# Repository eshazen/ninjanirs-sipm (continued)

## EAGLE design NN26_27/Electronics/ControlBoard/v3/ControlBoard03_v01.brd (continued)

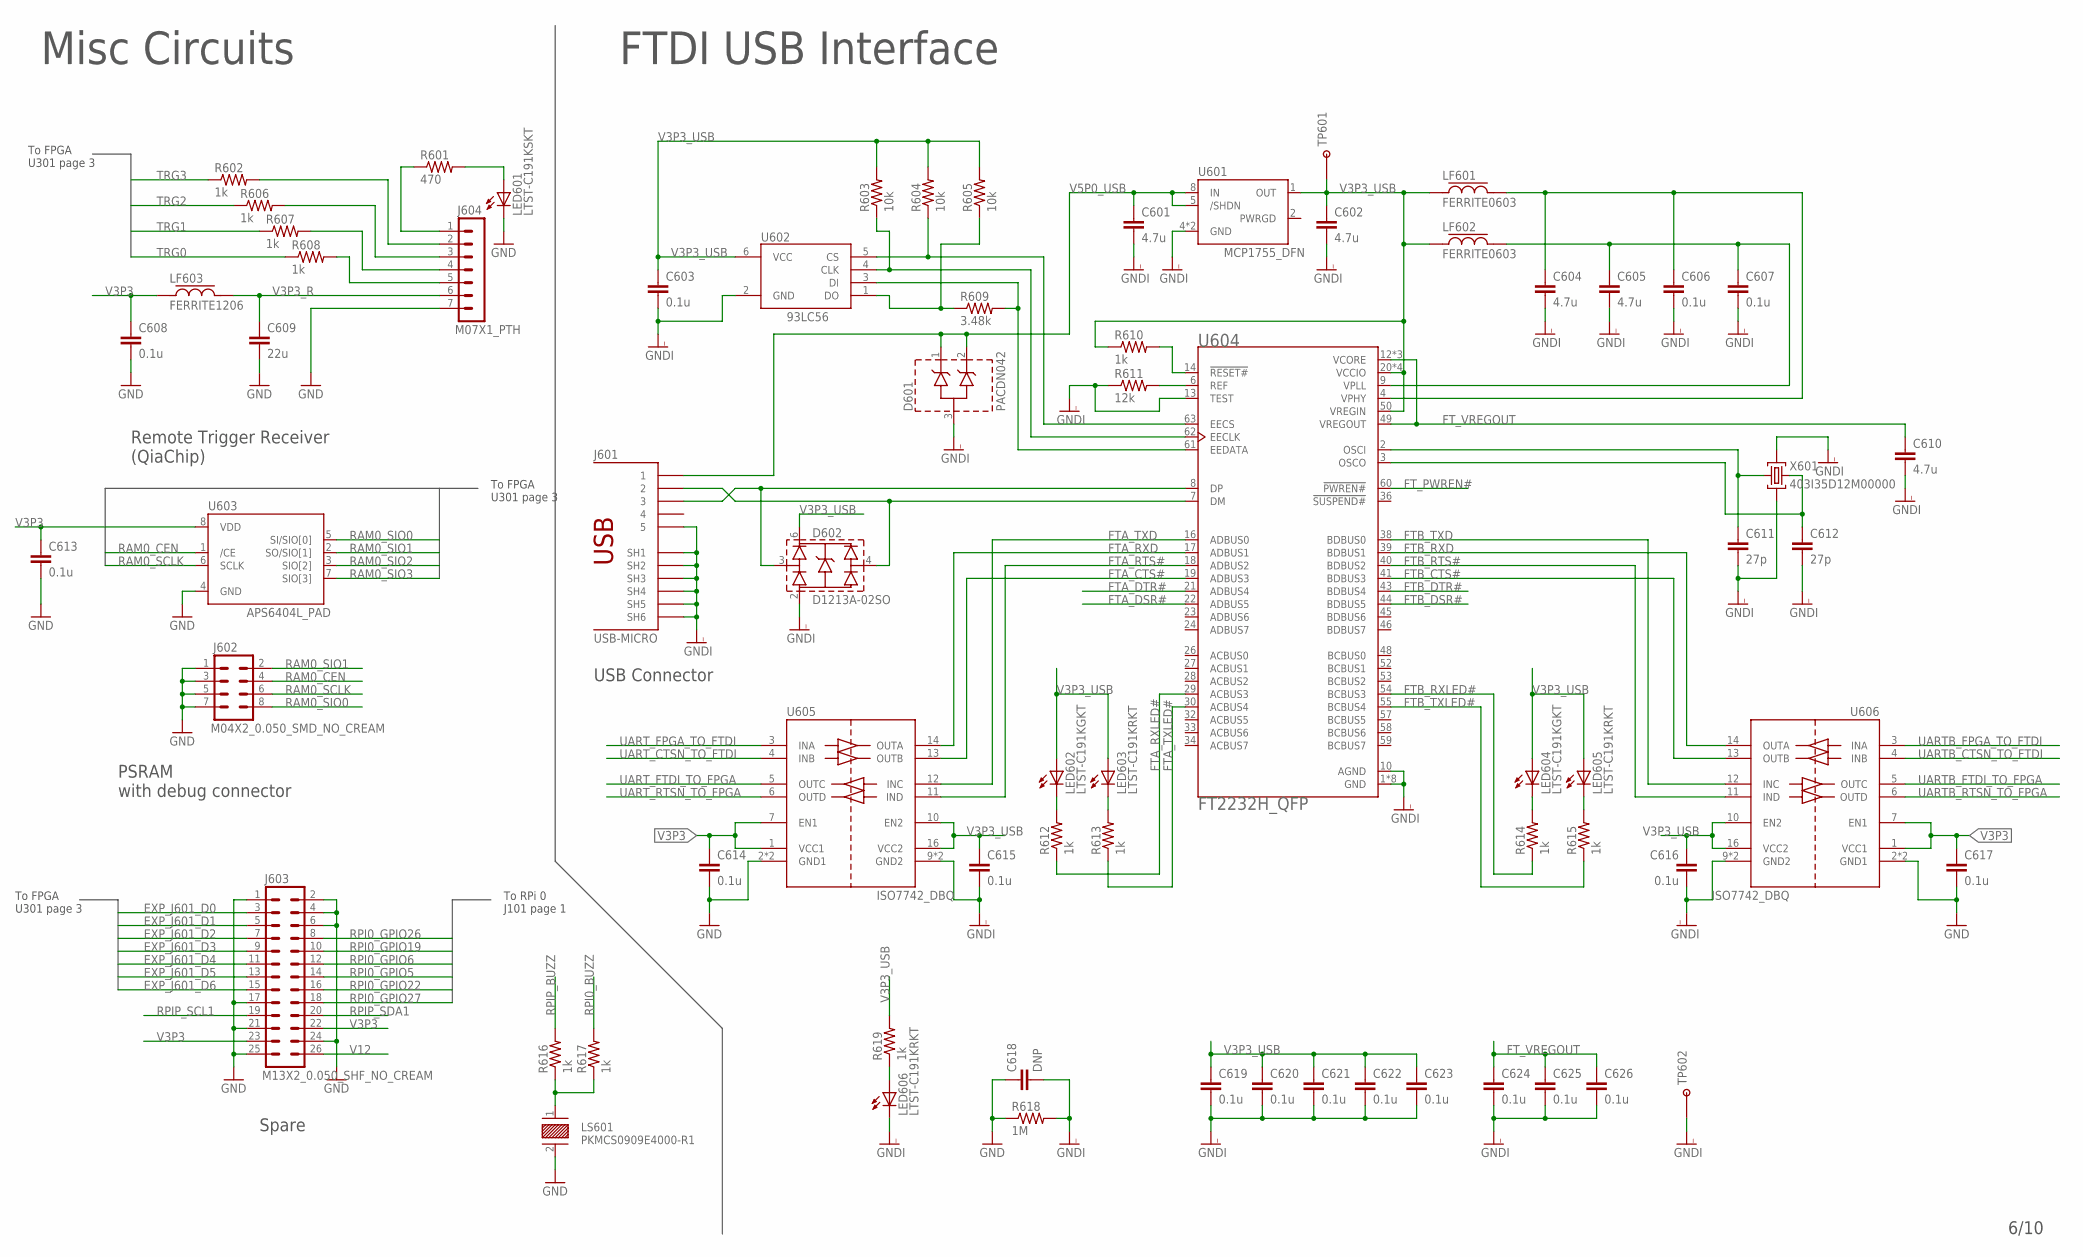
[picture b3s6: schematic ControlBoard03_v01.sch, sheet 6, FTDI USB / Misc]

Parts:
C601, C602, C604, C605, C610: 4.7u; 0402-CAP
C603, C606, C607, C608, C613, C614, C615, C616, C617, C619, C620, C621, C622, C623, C624, C625, C626: 0.1u; 0402-CAP
C609: 22u; 0805-CAP
C611, C612: 27p; 0402-CAP
C618: DNP; 1210
D601: PACDN042; SOT23-3
D602: D1213A-02SO; SOT23-6
J601: USB-MICRO
J602: M04X2_0.050_SMD_NO_CREAM
J603: M13X2_0.050_SHF_NO_CREAM
J604: M07X1_PTH
LED601: LTST-C191KSKT; LED-0603
LED602, LED604: LTST-C191KGKT; LED-0603
LED603, LED605, LED606: LTST-C191KRKT; LED-0603
LF601, LF602: FERRITE0603; 0603-FER
LF603: FERRITE1206; 1206
LS601: PKMCS0909E4000-R1; XDCR_PKMCS0909E4000-R1
R601: 470; 0402-RES
R602, R606, R607, R608, R610, R612, R613, R614, R615, R616, R617, R619: 1k; 0402-RES
R603, R604, R605: 10k; 0402-RES
R609: 3.48k; 0402-RES
R611: 12k; 0402-RES
R618: 1M; R2010
TP601: TESTPOINT_ROUND; TESTPAD_ROUND
TP602: TESTPOINT1X01; 1X01
U601: MCP1755_DFN; DFN8_2X3MM
U602: 93LC56; SOT23-6
U603: APS6404L_PAD; USON8L-2X3MM_APM
U604: FT2232H_QFP; QFP50P1200X1200X160-64N
U605, U606: ISO7742_DBQ; SSOP16
X601: 403I35D12M00000; CRYSTAL-3.2-2.5

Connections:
EXP_J601_D0: J603.3; also elsewhere on the board
EXP_J601_D1: J603.5; also elsewhere on the board
EXP_J601_D2: J603.7; also elsewhere on the board
EXP_J601_D3: J603.9; also elsewhere on the board
EXP_J601_D4: J603.11; also elsewhere on the board
EXP_J601_D5: J603.13; also elsewhere on the board
EXP_J601_D6: J603.15; also elsewhere on the board
FTA_CTS#: U604.19 (ADBUS3), U605.13 (OUTB)
FTA_DSR#: U604.22 (ADBUS5)
FTA_DTR#: U604.21 (ADBUS4)
FTA_RTS#: U604.18 (ADBUS2), U605.11 (IND)
FTA_RXD: U604.17 (ADBUS1), U605.14 (OUTA)
FTA_RXLED#: R612.1, U604.29 (ACBUS3)
FTA_TXD: U604.16 (ADBUS0), U605.12 (INC)
FTA_TXLED#: R613.1, U604.30 (ACBUS4)
FTB_CTS#: U604.41 (BDBUS3), U606.13 (OUTB)
FTB_DSR#: U604.44 (BDBUS5)
FTB_DTR#: U604.43 (BDBUS4)
FTB_RTS#: U604.40 (BDBUS2), U606.11 (IND)
FTB_RXD: U604.39 (BDBUS1), U606.14 (OUTA)
FTB_RXLED#: R614.1, U604.54 (BCBUS3)
FTB_TXD: U604.38 (BDBUS0), U606.12 (INC)
FTB_TXLED#: R615.1, U604.55 (BCBUS4)
FT_PWREN#: U604.60 (!PWREN#)
FT_VREGOUT: C610.1, C624.1, C625.1, C626.1, U604.12 (VCORE), U604.37 (VCORE), U604.49 (VREGOUT), U604.64 (VCORE)
GND: C608.2, C609.2, C613.2, C614.2, C617.2, C618.1, J602.1, J602.3, J602.5, J602.7, J603.1, J603.2, J603.4, J603.6, J603.17, J603.21, J603.24, J603.25, J604.7, LED601.C, LS601.2, R618.1, U603.4 (GND), U605.2 (GND1), U605.8 (GND1), U606.2 (GND1), U606.8 (GND1); also elsewhere on the board
GNDI: C601.2, C602.2, C603.2, C604.2, C605.2, C606.2, C607.2, C610.2, C611.2, C612.2, C615.2, C616.2, C618.2, C619.2, C620.2, C621.2, C622.2, C623.2, C624.2, C625.2, C626.2, D601.3 (A), D602.2 (VN), J601.5, J601.SH1, J601.SH2, J601.SH3, J601.SH4, J601.SH5, J601.SH6, LED606.C, R611.1, R618.2, TP602.1, U601.4 (GND), U601.P (GND), U602.2 (GND), U604.1 (GND), U604.5 (GND), U604.10 (AGND), U604.11 (GND), U604.13 (TEST), U604.15 (GND), U604.25 (GND), U604.35 (GND), U604.47 (GND), U604.51 (GND), U605.9 (GND2), U605.15 (GND2), U606.9 (GND2), U606.15 (GND2), X601.2 (GND), X601.4 (GND)
LED: J604.1, R601.1
unnamed: LED606.A, R619.1
unnamed: R604.1, U602.5 (CS), U604.63 (EECS)
unnamed: R603.1, U602.4 (CLK), U604.62 (EECLK)
unnamed: R605.1, R609.1, U602.1 (DO)
unnamed: LS601.1, R616.1, R617.1
unnamed: R609.2, U602.3 (DI), U604.61 (EEDATA)
unnamed: C605.1, C607.1, LF602.2, U604.9 (VPLL)
unnamed: C604.1, C606.1, LF601.2, U604.4 (VPHY)
unnamed: R610.2, U604.14 (!RESET#)
unnamed: R611.2, U604.6 (REF)
unnamed: C611.1, U604.2 (OSCI), X601.1 (C1)
unnamed: C612.1, U604.3 (OSCO), X601.3 (C2)
unnamed: LED604.C, R614.2
unnamed: LED605.C, R615.2
unnamed: LED602.C, R612.2
unnamed: LED603.C, R613.2
unnamed: D602.3 (CH1), J601.3, U604.8 (DP)
unnamed: D602.4 (CH2), J601.2, U604.7 (DM)
unnamed: J604.5, R608.2
unnamed: J604.4, R607.2
unnamed: J604.3, R606.2
unnamed: J604.2, R602.2
unnamed: LED601.A, R601.2
RAM0_CEN: J602.4, U603.1 (/CE); also elsewhere on the board
RAM0_SCLK: J602.6, U603.6 (SCLK); also elsewhere on the board
RAM0_SIO0: J602.8, U603.5 (SI/SIO[0]); also elsewhere on the board
RAM0_SIO1: J602.2, U603.2 (SO/SIO[1]); also elsewhere on the board
RAM0_SIO2: U603.3 (SIO[2]); also elsewhere on the board
RAM0_SIO3: U603.7 (SIO[3]); also elsewhere on the board
RPI0_BUZZ: R617.2; also elsewhere on the board
RPI0_GPIO5: J603.14; also elsewhere on the board
RPI0_GPIO6: J603.12; also elsewhere on the board
RPI0_GPIO19: J603.10; also elsewhere on the board
RPI0_GPIO22: J603.16; also elsewhere on the board
RPI0_GPIO26: J603.8; also elsewhere on the board
RPI0_GPIO27: J603.18; also elsewhere on the board
RPIP_BUZZ: R616.2; also elsewhere on the board
RPIP_SCL1: J603.19; also elsewhere on the board
RPIP_SDA1: J603.20; also elsewhere on the board
TRG0: R608.1; also elsewhere on the board
TRG1: R607.1; also elsewhere on the board
TRG2: R606.1; also elsewhere on the board
TRG3: R602.1; also elsewhere on the board
UARTB_CTSN_TO_FTDI: U606.4 (INB); also elsewhere on the board
UARTB_FPGA_TO_FTDI: U606.3 (INA); also elsewhere on the board
UARTB_FTDI_TO_FPGA: U606.5 (OUTC); also elsewhere on the board
UARTB_RTSN_TO_FPGA: U606.6 (OUTD); also elsewhere on the board
UART_CTSN_TO_FTDI: U605.4 (INB); also elsewhere on the board
UART_FPGA_TO_FTDI: U605.3 (INA); also elsewhere on the board
UART_FTDI_TO_FPGA: U605.5 (OUTC); also elsewhere on the board
UART_RTSN_TO_FPGA: U605.6 (OUTD); also elsewhere on the board
V3P3: C608.1, C613.1, C614.1, C617.1, J603.22, J603.23, LF603.1, U603.8 (VDD), U605.1 (VCC1), U605.7 (EN1), U606.1 (VCC1), U606.7 (EN1); also elsewhere on the board
V3P3_R: C609.1, J604.6, LF603.2
V3P3_USB: C602.1, C603.1, C615.1, C616.1, C619.1, C620.1, C621.1, C622.1, C623.1, D602.6 (VP), LED602.A, LED603.A, LED604.A, LED605.A, LF601.1, LF602.1, R603.2, R604.2, R605.2, R610.1, R619.2, TP601.P$1, U601.1 (OUT), U602.6 (VCC), U604.20 (VCCIO), U604.31 (VCCIO), U604.42 (VCCIO), U604.50 (VREGIN), U604.56 (VCCIO), U605.10 (EN2), U605.16 (VCC2), U606.10 (EN2), U606.16 (VCC2)
V5P0_USB: C601.1, D601.1 (C), D601.2 (C), J601.1, U601.5 (/SHDN), U601.8 (IN)
V12: J603.26; also elsewhere on the board

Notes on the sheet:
Misc Circuits
Remote Trigger Receiver (QiaChip)
PSRAM with debug connector
Spare
To FPGA U301 page 3
To RPi 0 J101 page 1
FTDI USB Interface
USB Connector

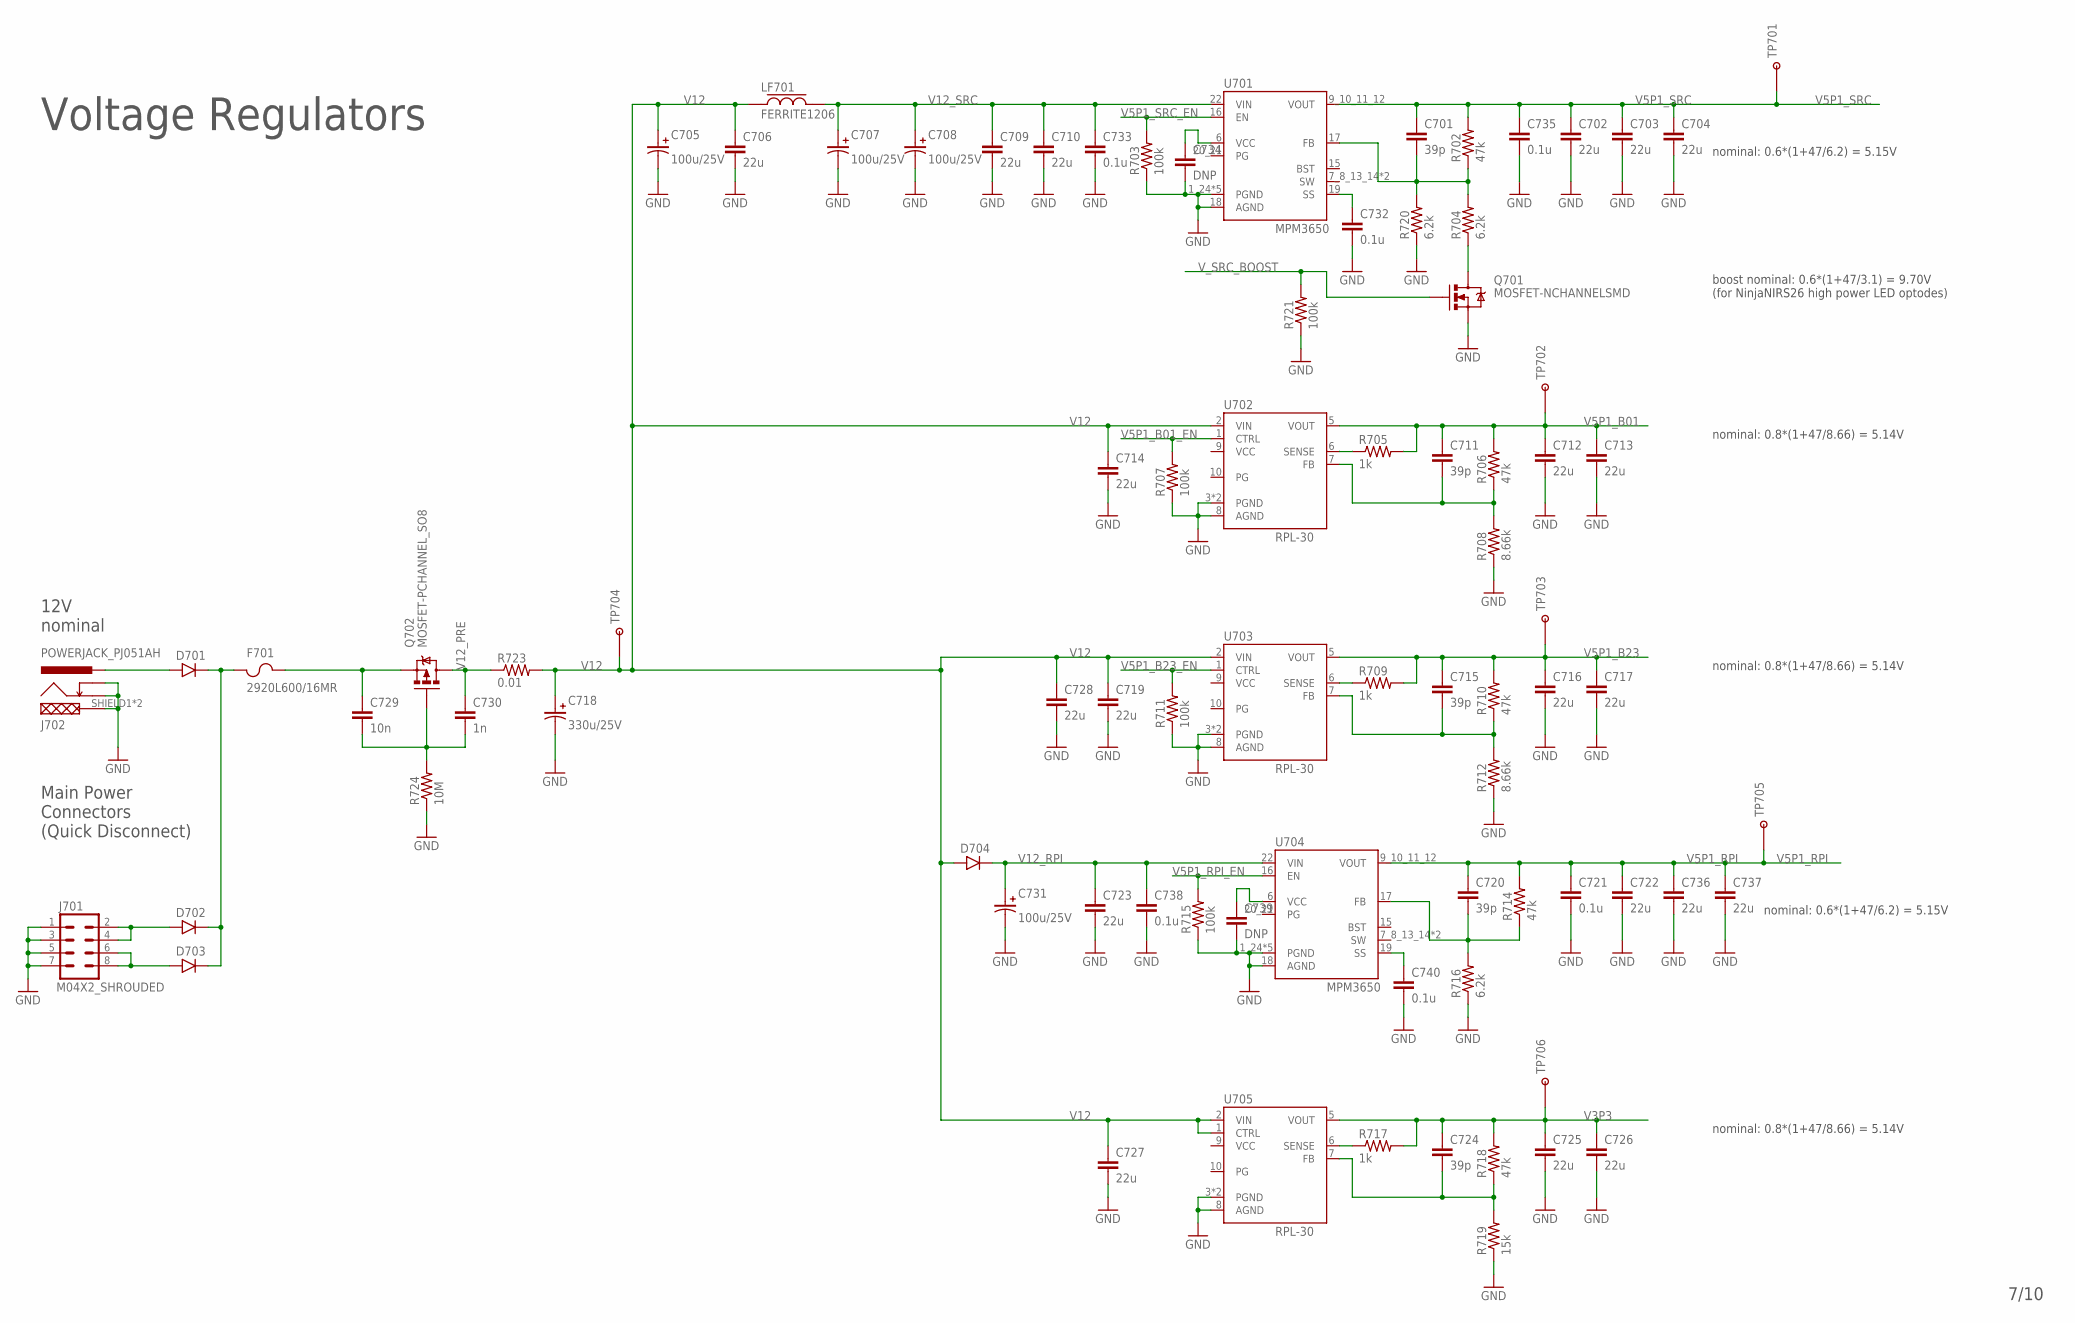
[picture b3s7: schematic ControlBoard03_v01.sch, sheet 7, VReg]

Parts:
C701, C711, C715, C720, C724: 39p; 0402-CAP
C702, C703, C704, C706, C709, C710, C712, C713, C714, C716, C717, C719, C722, C723, C725, C726, C727, C728, C736, C737: 22u; 0805-CAP
C705, C707, C708, C731: 100u/25V; 2917-CAP
C718: 330u/25V; CAP-SMD-POL-8X10
C721, C732, C733, C735, C738, C740: 0.1u; 0402-CAP
C729: 10n; 0603-CAP
C730: 1n; 0603-CAP
C734, C739: DNP; 0402-CAP
D701, D702, D703, D704: DIODESOD128; SOD128
F701: 2920L600/16MR; 2920-FUSE
J701: M04X2_SHROUDED; M04X2-SHROUDED
J702: POWERJACK_PJ051AH; PJ051AH
LF701: FERRITE1206; 1206
Q701: MOSFET-NCHANNELSMD; SOT23-3
Q702: MOSFET-PCHANNEL_SO8; SO08
R702, R706, R710, R714, R718: 47k; 0402-RES
R703, R707, R711, R715, R721: 100k; 0402-RES
R704, R716, R720: 6.2k; 0402-RES
R705, R709, R717: 1k; 0402-RES
R708, R712: 8.66k; 0402-RES
R719: 15k; 0402-RES
R723: 0.01; 1206
R724: 10M; 0805
TP701, TP702, TP703, TP704, TP705, TP706: TESTPOINT_ROUND; TESTPAD_ROUND
U701, U704: MPM3650; QFN-24-MPS_FULL_CREAM
U702, U703, U705: RPL-30

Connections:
GND: C702.2, C703.2, C704.2, C705.N, C706.2, C707.N, C708.N, C709.2, C710.2, C712.2, C713.2, C714.2, C716.2, C717.2, C718.N, C719.2, C721.2, C722.2, C723.2, C725.2, C726.2, C727.2, C728.2, C731.N, C732.2, C733.2, C734.2, C735.2, C736.2, C737.2, C738.2, C739.2, C740.2, J701.1, J701.3, J701.5, J701.7, J702.SHIELD1 (SHIELD), J702.SHIELD2 (SHIELD), J702.SLEEVE (GND), J702.SWITCH (GNDBREAK), Q701.2 (S), R703.1, R707.1, R708.1, R711.1, R712.1, R715.1, R716.1, R719.1, R720.1, R721.1, R724.1, U701.1_24 (PGND), U701.2 (PGND), U701.3 (PGND), U701.4 (PGND), U701.5 (PGND), U701.18 (AGND), U702.3 (PGND), U702.4 (PGND), U702.8 (AGND), U703.3 (PGND), U703.4 (PGND), U703.8 (AGND), U704.1_24 (PGND), U704.2 (PGND), U704.3 (PGND), U704.4 (PGND), U704.5 (PGND), U704.18 (AGND), U705.3 (PGND), U705.4 (PGND), U705.8 (AGND); also elsewhere on the board
unnamed: C701.2, R702.1, R704.2, R720.2, U701.17 (FB)
unnamed: Q701.3 (D), R704.1
unnamed: C720.2, R714.1, R716.2, U704.17 (FB)
unnamed: D701.A, J702.CENTER (PWR)
unnamed: C711.2, R706.1, R708.2, U702.7 (FB)
unnamed: R705.1, U702.6 (SENSE)
unnamed: C715.2, R710.1, R712.2, U703.7 (FB)
unnamed: R709.1, U703.6 (SENSE)
unnamed: C739.1, U704.6 (VCC)
unnamed: C740.1, U704.19 (SS)
unnamed: C724.2, R718.1, R719.2, U705.7 (FB)
unnamed: R717.1, U705.6 (SENSE)
unnamed: C734.1, U701.6 (VCC)
unnamed: D702.A, J701.2, J701.4
unnamed: C729.1, F701.2, Q702.1 (S), Q702.2 (S), Q702.3 (S)
unnamed: D703.A, J701.6, J701.8
unnamed: D701.C, D702.C, D703.C, F701.1
unnamed: C729.2, C730.2, Q702.4 (G), R724.2
unnamed: C732.1, U701.19 (SS)
V3P3: C724.1, C725.1, C726.1, R717.2, R718.2, TP706.P$1, U705.5 (VOUT); also elsewhere on the board
V5P1_B01: C711.1, C712.1, C713.1, R705.2, R706.2, TP702.P$1, U702.5 (VOUT); also elsewhere on the board
V5P1_B01_EN: R707.2, U702.1 (CTRL); also elsewhere on the board
V5P1_B23: C715.1, C716.1, C717.1, R709.2, R710.2, TP703.P$1, U703.5 (VOUT); also elsewhere on the board
V5P1_B23_EN: R711.2, U703.1 (CTRL); also elsewhere on the board
V5P1_RPI: C720.1, C721.1, C722.1, C736.1, C737.1, R714.2, TP705.P$1, U704.9_10_11_12 (VOUT); also elsewhere on the board
V5P1_RPI_EN: R715.2, U704.16 (EN); also elsewhere on the board
V5P1_SRC: C701.1, C702.1, C703.1, C704.1, C735.1, R702.2, TP701.P$1, U701.9_10_11_12 (VOUT); also elsewhere on the board
V5P1_SRC_EN: R703.2, U701.16 (EN); also elsewhere on the board
V12: C705.P, C706.1, C714.1, C718.P, C719.1, C727.1, C728.1, D704.A, LF701.1, R723.2, TP704.P$1, U702.2 (VIN), U703.2 (VIN), U705.1 (CTRL), U705.2 (VIN); also elsewhere on the board
V12_PRE: C730.1, Q702.5 (D), Q702.6 (D), Q702.7 (D), Q702.8 (D), R723.1; also elsewhere on the board
V12_RPI: C723.1, C731.P, C738.1, D704.C, U704.22 (VIN)
V12_SRC: C707.P, C708.P, C709.1, C710.1, C733.1, LF701.2, U701.22 (VIN)
V_SRC_BOOST: Q701.1 (G), R721.2; also elsewhere on the board

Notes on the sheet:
Main Power Connectors (Quick Disconnect)
12V nominal
Voltage Regulators
nominal: 0.6*(1+47/6.2) = 5.15V
nominal: 0.8*(1+47/8.66) = 5.14V
boost nominal: 0.6*(1+47/3.1) = 9.70V (for NinjaNIRS26 high power LED optodes)

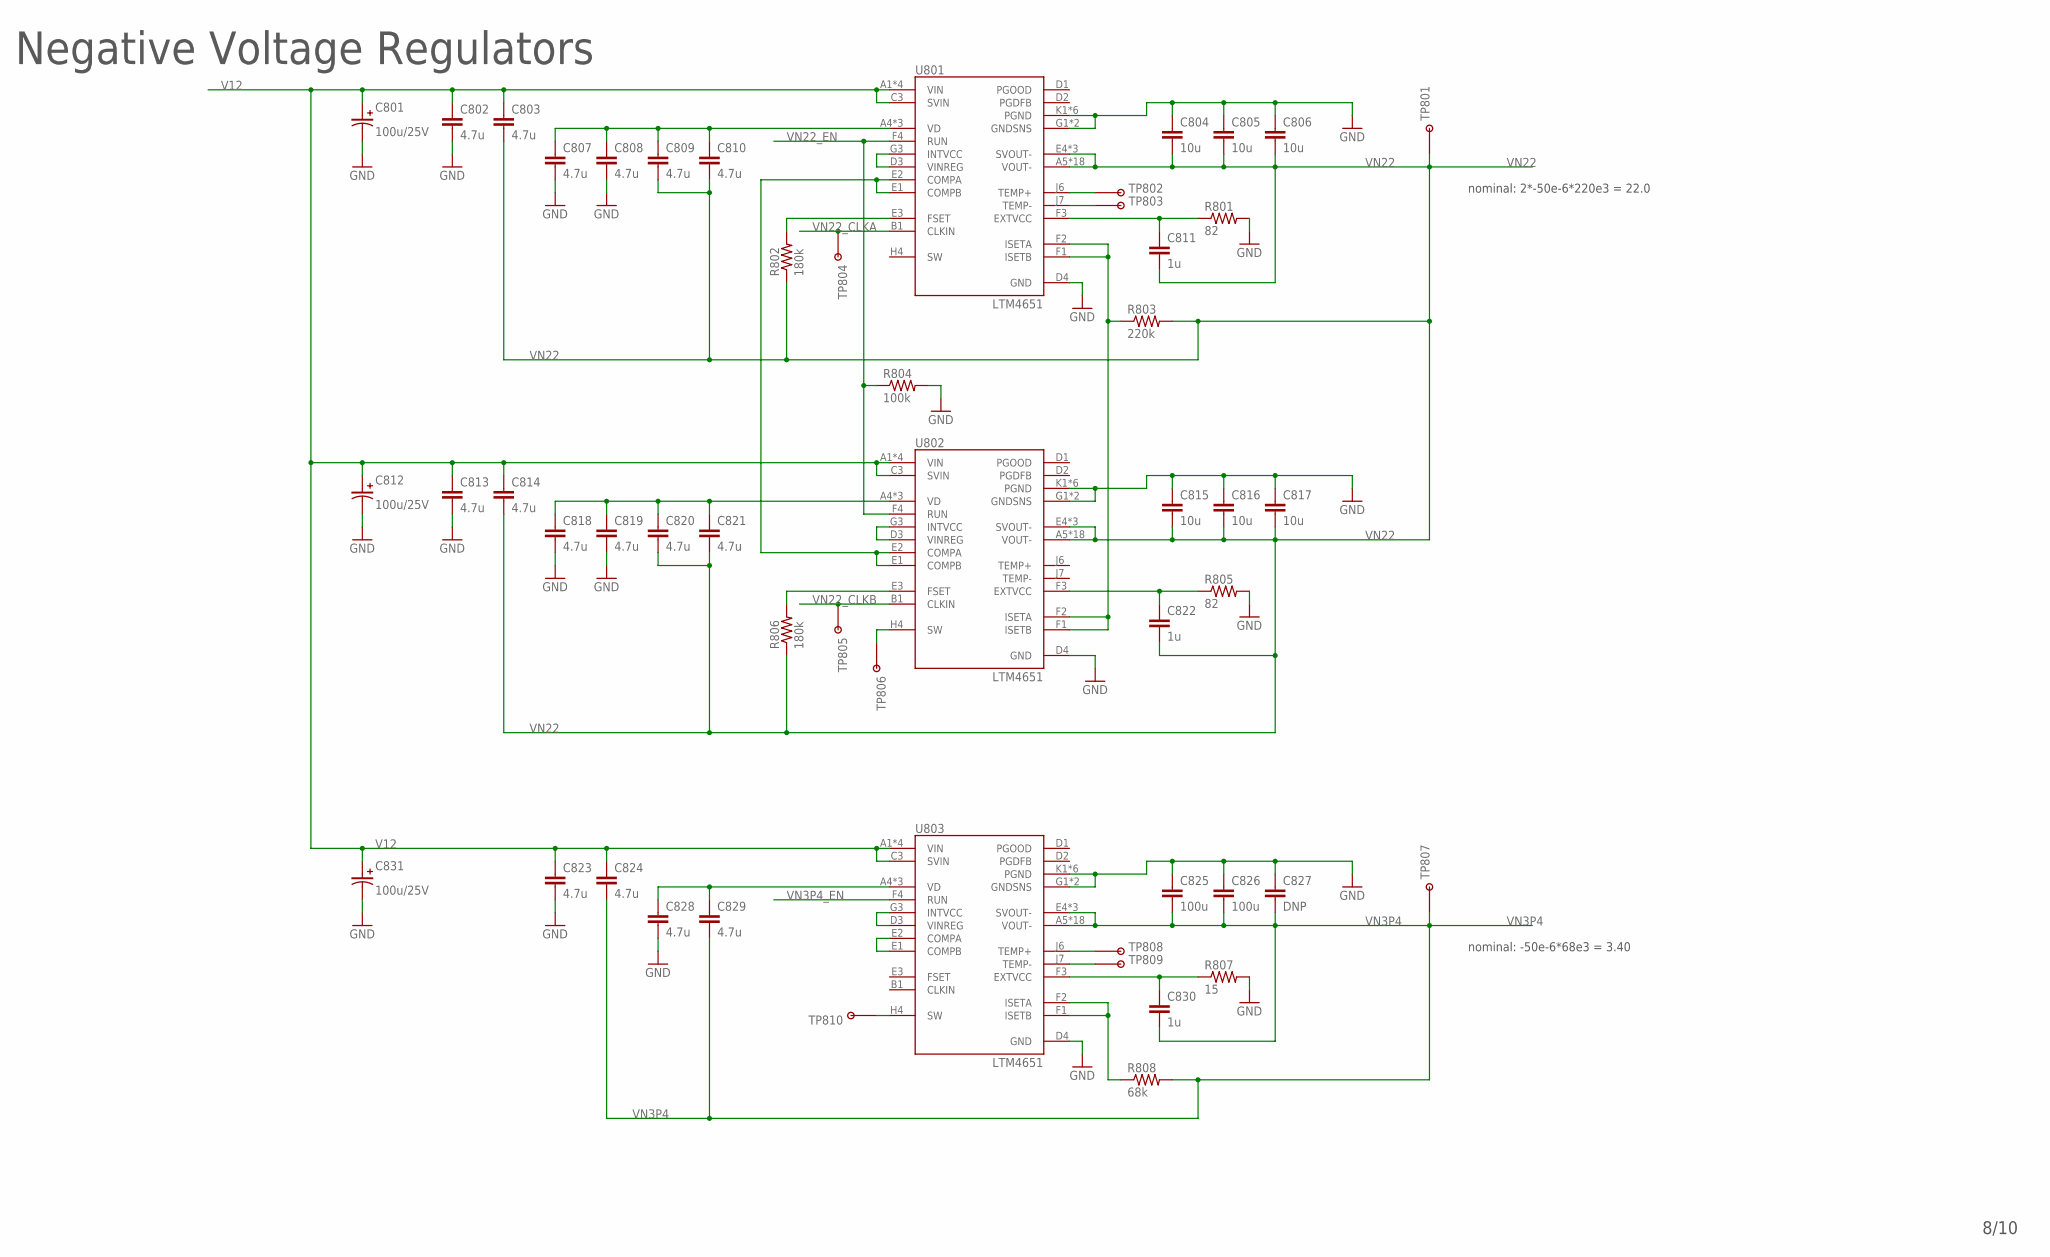
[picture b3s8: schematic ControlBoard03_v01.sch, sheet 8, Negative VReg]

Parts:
C801, C812, C831: 100u/25V; 2917-CAP
C802, C803, C807, C808, C809, C810, C813, C814, C818, C819, C820, C821, C823, C824, C828, C829: 4.7u; 0805-CAP
C804, C805, C806, C815, C816, C817: 10u; 1206
C811, C822, C830: 1u; 0603-CAP
C825, C826: 100u; 1206
C827: DNP; 1206
R801, R805: 82; 0402-RES
R802, R806: 180k; 0402-RES
R803: 220k; 0402-RES
R804: 100k; 0402-RES
R807: 15; 0402-RES
R808: 68k; 0402-RES
TP801, TP802, TP803, TP804, TP805, TP806, TP807, TP808, TP809, TP810: TESTPOINT_ROUND; TESTPAD_ROUND
U801, U802, U803: LTM4651; BGA-77

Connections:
GND: C801.N, C802.2, C804.1, C805.1, C806.1, C807.2, C808.2, C812.N, C813.2, C815.1, C816.1, C817.1, C818.2, C819.2, C823.2, C825.1, C826.1, C827.1, C828.2, C831.N, R801.2, R804.2, R805.2, R807.2, U801.D4 (GND), U801.G1 (GNDSNS), U801.H1 (GNDSNS), U801.K1 (PGND), U801.K2 (PGND), U801.K3 (PGND), U801.L1 (PGND), U801.L2 (PGND), U801.L3 (PGND), U802.D4 (GND), U802.G1 (GNDSNS), U802.H1 (GNDSNS), U802.K1 (PGND), U802.K2 (PGND), U802.K3 (PGND), U802.L1 (PGND), U802.L2 (PGND), U802.L3 (PGND), U803.D4 (GND), U803.G1 (GNDSNS), U803.H1 (GNDSNS), U803.K1 (PGND), U803.K2 (PGND), U803.K3 (PGND), U803.L1 (PGND), U803.L2 (PGND), U803.L3 (PGND); also elsewhere on the board
unnamed: U803.D3 (VINREG), U803.G3 (INTVCC)
unnamed: TP802.P$1, U801.J6 (TEMP+)
unnamed: U803.E1 (COMPB), U803.E2 (COMPA)
unnamed: U801.D3 (VINREG), U801.G3 (INTVCC)
unnamed: U801.E1 (COMPB), U801.E2 (COMPA), U802.E1 (COMPB), U802.E2 (COMPA)
unnamed: R802.2, U801.E3 (FSET)
unnamed: TP803.P$1, U801.J7 (TEMP-)
unnamed: C811.1, R801.1, U801.F3 (EXTVCC)
unnamed: C822.1, R805.1, U802.F3 (EXTVCC)
unnamed: TP808.P$1, U803.J6 (TEMP+)
unnamed: TP809.P$1, U803.J7 (TEMP-)
unnamed: R803.1, U801.F1 (ISETB), U801.F2 (ISETA), U802.F1 (ISETB), U802.F2 (ISETA)
unnamed: U802.D3 (VINREG), U802.G3 (INTVCC)
unnamed: TP806.P$1, U802.H4 (SW)
unnamed: C830.1, R807.1, U803.F3 (EXTVCC)
unnamed: C807.1, C808.1, C809.1, C810.1, U801.A4 (VD), U801.B4 (VD), U801.C4 (VD)
unnamed: C818.1, C819.1, C820.1, C821.1, U802.A4 (VD), U802.B4 (VD), U802.C4 (VD)
unnamed: R806.2, U802.E3 (FSET)
unnamed: R808.1, U803.F1 (ISETB), U803.F2 (ISETA)
unnamed: TP810.P$1, U803.H4 (SW)
unnamed: C828.1, C829.1, U803.A4 (VD), U803.B4 (VD), U803.C4 (VD)
V12: C801.P, C802.1, C803.1, C812.P, C813.1, C814.1, C823.1, C824.1, C831.P, U801.A1 (VIN), U801.A2 (VIN), U801.A3 (VIN), U801.B3 (VIN), U801.C3 (SVIN), U802.A1 (VIN), U802.A2 (VIN), U802.A3 (VIN), U802.B3 (VIN), U802.C3 (SVIN), U803.A1 (VIN), U803.A2 (VIN), U803.A3 (VIN), U803.B3 (VIN), U803.C3 (SVIN); also elsewhere on the board
VN3P4: C824.2, C825.2, C826.2, C827.2, C829.2, C830.2, R808.2, TP807.P$1, U803.A5 (VOUT-), U803.B5 (VOUT-), U803.C2 (VOUT-), U803.C5 (VOUT-), U803.D5 (VOUT-), U803.E4 (SVOUT-), U803.E5 (VOUT-), U803.F5 (VOUT-), U803.G2 (SVOUT-), U803.G4 (VOUT-), U803.G5 (VOUT-), U803.H2 (SVOUT-), U803.H3 (VOUT-), U803.H5 (VOUT-), U803.J3 (VOUT-), U803.J4 (VOUT-), U803.J5 (VOUT-), U803.K4 (VOUT-), U803.K5 (VOUT-), U803.L4 (VOUT-), U803.L5 (VOUT-); also elsewhere on the board
VN3P4_EN: U803.F4 (RUN); also elsewhere on the board
VN22: C803.2, C804.2, C805.2, C806.2, C809.2, C810.2, C811.2, C814.2, C815.2, C816.2, C817.2, C820.2, C821.2, C822.2, R802.1, R803.2, R806.1, TP801.P$1, U801.A5 (VOUT-), U801.B5 (VOUT-), U801.C2 (VOUT-), U801.C5 (VOUT-), U801.D5 (VOUT-), U801.E4 (SVOUT-), U801.E5 (VOUT-), U801.F5 (VOUT-), U801.G2 (SVOUT-), U801.G4 (VOUT-), U801.G5 (VOUT-), U801.H2 (SVOUT-), U801.H3 (VOUT-), U801.H5 (VOUT-), U801.J3 (VOUT-), U801.J4 (VOUT-), U801.J5 (VOUT-), U801.K4 (VOUT-), U801.K5 (VOUT-), U801.L4 (VOUT-), U801.L5 (VOUT-), U802.A5 (VOUT-), U802.B5 (VOUT-), U802.C2 (VOUT-), U802.C5 (VOUT-), U802.D5 (VOUT-), U802.E4 (SVOUT-), U802.E5 (VOUT-), U802.F5 (VOUT-), U802.G2 (SVOUT-), U802.G4 (VOUT-), U802.G5 (VOUT-), U802.H2 (SVOUT-), U802.H3 (VOUT-), U802.H5 (VOUT-), U802.J3 (VOUT-), U802.J4 (VOUT-), U802.J5 (VOUT-), U802.K4 (VOUT-), U802.K5 (VOUT-), U802.L4 (VOUT-), U802.L5 (VOUT-); also elsewhere on the board
VN22_CLKA: TP804.P$1, U801.B1 (CLKIN); also elsewhere on the board
VN22_CLKB: TP805.P$1, U802.B1 (CLKIN); also elsewhere on the board
VN22_EN: R804.1, U801.F4 (RUN), U802.F4 (RUN); also elsewhere on the board

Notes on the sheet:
Negative Voltage Regulators
nominal: -50e-6*68e3 = 3.40
nominal: 2*-50e-6*220e3 = 22.0

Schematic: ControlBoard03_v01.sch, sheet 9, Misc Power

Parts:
C901, C902, C903, C915, C944: 22u; 0805-CAP
C904, C905, C906, C907, C908, C909, C910, C911, C912, C913, C914: 4.7u; 0402-CAP
C916, C917, C918, C919, C920, C921, C922, C923, C924, C925, C926, C927, C928, C929, C930, C931, C932, C933, C934, C935, C936, C937, C938, C939, C940, C941, C942, C945, C947, C948: 0.1u; 0402-CAP
C943: 39p; 0402-CAP
C946: DNP; 0402-CAP
FID901, FID902, FID903, FID904, FID905, FID906, FID907: FIDUCIALUFIDUCIAL; MICRO-FIDUCIAL
J901: M05X2_SMD_0.050_NOCREAM; M05X2_0.050_SMD_NO_CREAM
LED901: LTST-C191KGKT; LED-0603
R901: 47k; 0402-RES
R902: 100k; 0402-RES
R904: 3.48k; 0402-RES
R905: 100; 0402-RES
R906: 1k; 0402-RES
TP901, TP902: TESTPOINT_ROUND; TESTPAD_ROUND
TP903: TESTPOINTTUR; TURRET
U201: RP2040; QFN-56_EP
U301: MACHXO2_FTBGA256; LBGA-256
U901: MPM3650; QFN-24-MPS_FULL_CREAM

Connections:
GND: C901.2, C902.2, C903.2, C904.2, C905.2, C906.2, C907.2, C908.2, C909.2, C910.2, C911.2, C912.2, C913.2, C914.2, C915.2, C916.2, C917.2, C918.2, C919.2, C920.2, C921.2, C922.2, C923.2, C924.2, C925.2, C926.2, C927.2, C928.2, C929.2, C930.2, C931.2, C932.2, C933.2, C934.2, C935.2, C936.2, C937.2, C938.2, C939.2, C940.2, C941.2, C942.2, C944.2, C945.2, C946.2, C947.2, C948.2, J901.2, J901.4, J901.6, LED901.C, R902.1, R904.1, TP903.P$1, U201.PAD (GND), U301.B2 (GND), U301.B15 (GND), U301.C3 (GND), U301.C14 (GND), U301.D4 (GND), U301.D13 (GND), U301.E5 (GND), U301.E12 (GND), U301.F6 (GND), U301.F11 (GND), U301.H8 (GND), U301.H9 (GND), U301.J8 (GND), U301.J9 (GND), U301.L6 (GND), U301.L11 (GND), U301.M5 (GND), U301.M12 (GND), U301.N4 (GND), U301.N13 (GND), U301.P3 (GND), U301.P14 (GND), U301.R2 (GND), U301.R15 (GND), U901.1_24 (PGND), U901.2 (PGND), U901.3 (PGND), U901.4 (PGND), U901.5 (PGND), U901.18 (AGND); also elsewhere on the board
J901_SPARE0: J901.8; also elsewhere on the board
J901_SPARE1: J901.9; also elsewhere on the board
J901_SPARE2: J901.10; also elsewhere on the board
unnamed: C947.1, U901.19 (SS)
unnamed: LED901.A, R906.1
unnamed: C906.1, R905.2, U201.43 (ADC_VDD)
unnamed: C946.1, U901.6 (VCC)
unnamed: C943.2, R901.1, R904.2, U901.17 (FB)
V1P1: C904.1, C916.1, C917.1, TP902.P$1, U201.23 (DVDD), U201.45 (VREG_VOUT), U201.50 (DVDD)
V3P3: C905.1, C907.1, C908.1, C909.1, C910.1, C911.1, C912.1, C913.1, C914.1, C915.1, C918.1, C919.1, C920.1, C921.1, C922.1, C923.1, C924.1, C925.1, C926.1, C927.1, C928.1, C929.1, C930.1, C931.1, C932.1, C933.1, C934.1, C935.1, C936.1, C937.1, C938.1, C939.1, C940.1, C941.1, C942.1, R905.1, R906.2, U201.1 (IOVDD), U201.10 (IOVDD), U201.22 (IOVDD), U201.33 (IOVDD), U201.42 (IOVDD), U201.44 (VREG_VIN), U201.48 (USB_VDD), U201.49 (IOVDD), U301.A1 (VCC), U301.A16 (VCC), U301.D5 (VCCIO0), U301.D12 (VCCIO0), U301.E4 (VCCIO5), U301.E13 (VCCIO1), U301.G7 (VCC), U301.G8 (VCCIO0), U301.G9 (VCCIO0), U301.G10 (VCC), U301.H7 (VCCIO4), U301.H10 (VCCIO1), U301.J7 (VCCIO4), U301.J10 (VCCIO1), U301.K7 (VCC), U301.K8 (VCCIO2), U301.K9 (VCCIO2), U301.K10 (VCC), U301.M4 (VCCIO3), U301.M13 (VCCIO1), U301.N5 (VCCIO2), U301.N12 (VCCIO2), U301.T1 (VCC), U301.T16 (VCC); also elsewhere on the board
V9P0: C902.1, C903.1, C943.1, C944.1, C948.1, R901.2, TP901.P$1, U901.9_10_11_12 (VOUT); also elsewhere on the board
V9P0_EN: R902.2, U901.16 (EN); also elsewhere on the board
V12: C901.1, C945.1, J901.5, J901.7, U901.22 (VIN); also elsewhere on the board
V60: J901.1, J901.3; also elsewhere on the board

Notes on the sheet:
Misc Power
0.6*(1+47/3.48)= 8.70V nominal
FPGA Decoupling
MCU Decoupling
Future SiPM bias module

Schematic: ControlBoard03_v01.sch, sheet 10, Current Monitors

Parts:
C1009, C1010: 0.1u; 0402-CAP
R1003: 470; 0402-RES
U1005: INA21X_DCK; SOT363

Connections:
GND: C1009.2, C1010.2, U1005.1 (REF), U1005.2 (GND); also elsewhere on the board
unnamed: R1003.1, U1005.6 (OUT)
V3P3: C1009.1, U1005.3 (V+); also elsewhere on the board
V12: U1005.5 (IN-); also elsewhere on the board
V12_CURR_SENSE: C1010.1, R1003.2; also elsewhere on the board
V12_PRE: U1005.4 (IN+); also elsewhere on the board

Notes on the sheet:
Current Monitors
System Total Current Monitor
INA214AIDCKR
